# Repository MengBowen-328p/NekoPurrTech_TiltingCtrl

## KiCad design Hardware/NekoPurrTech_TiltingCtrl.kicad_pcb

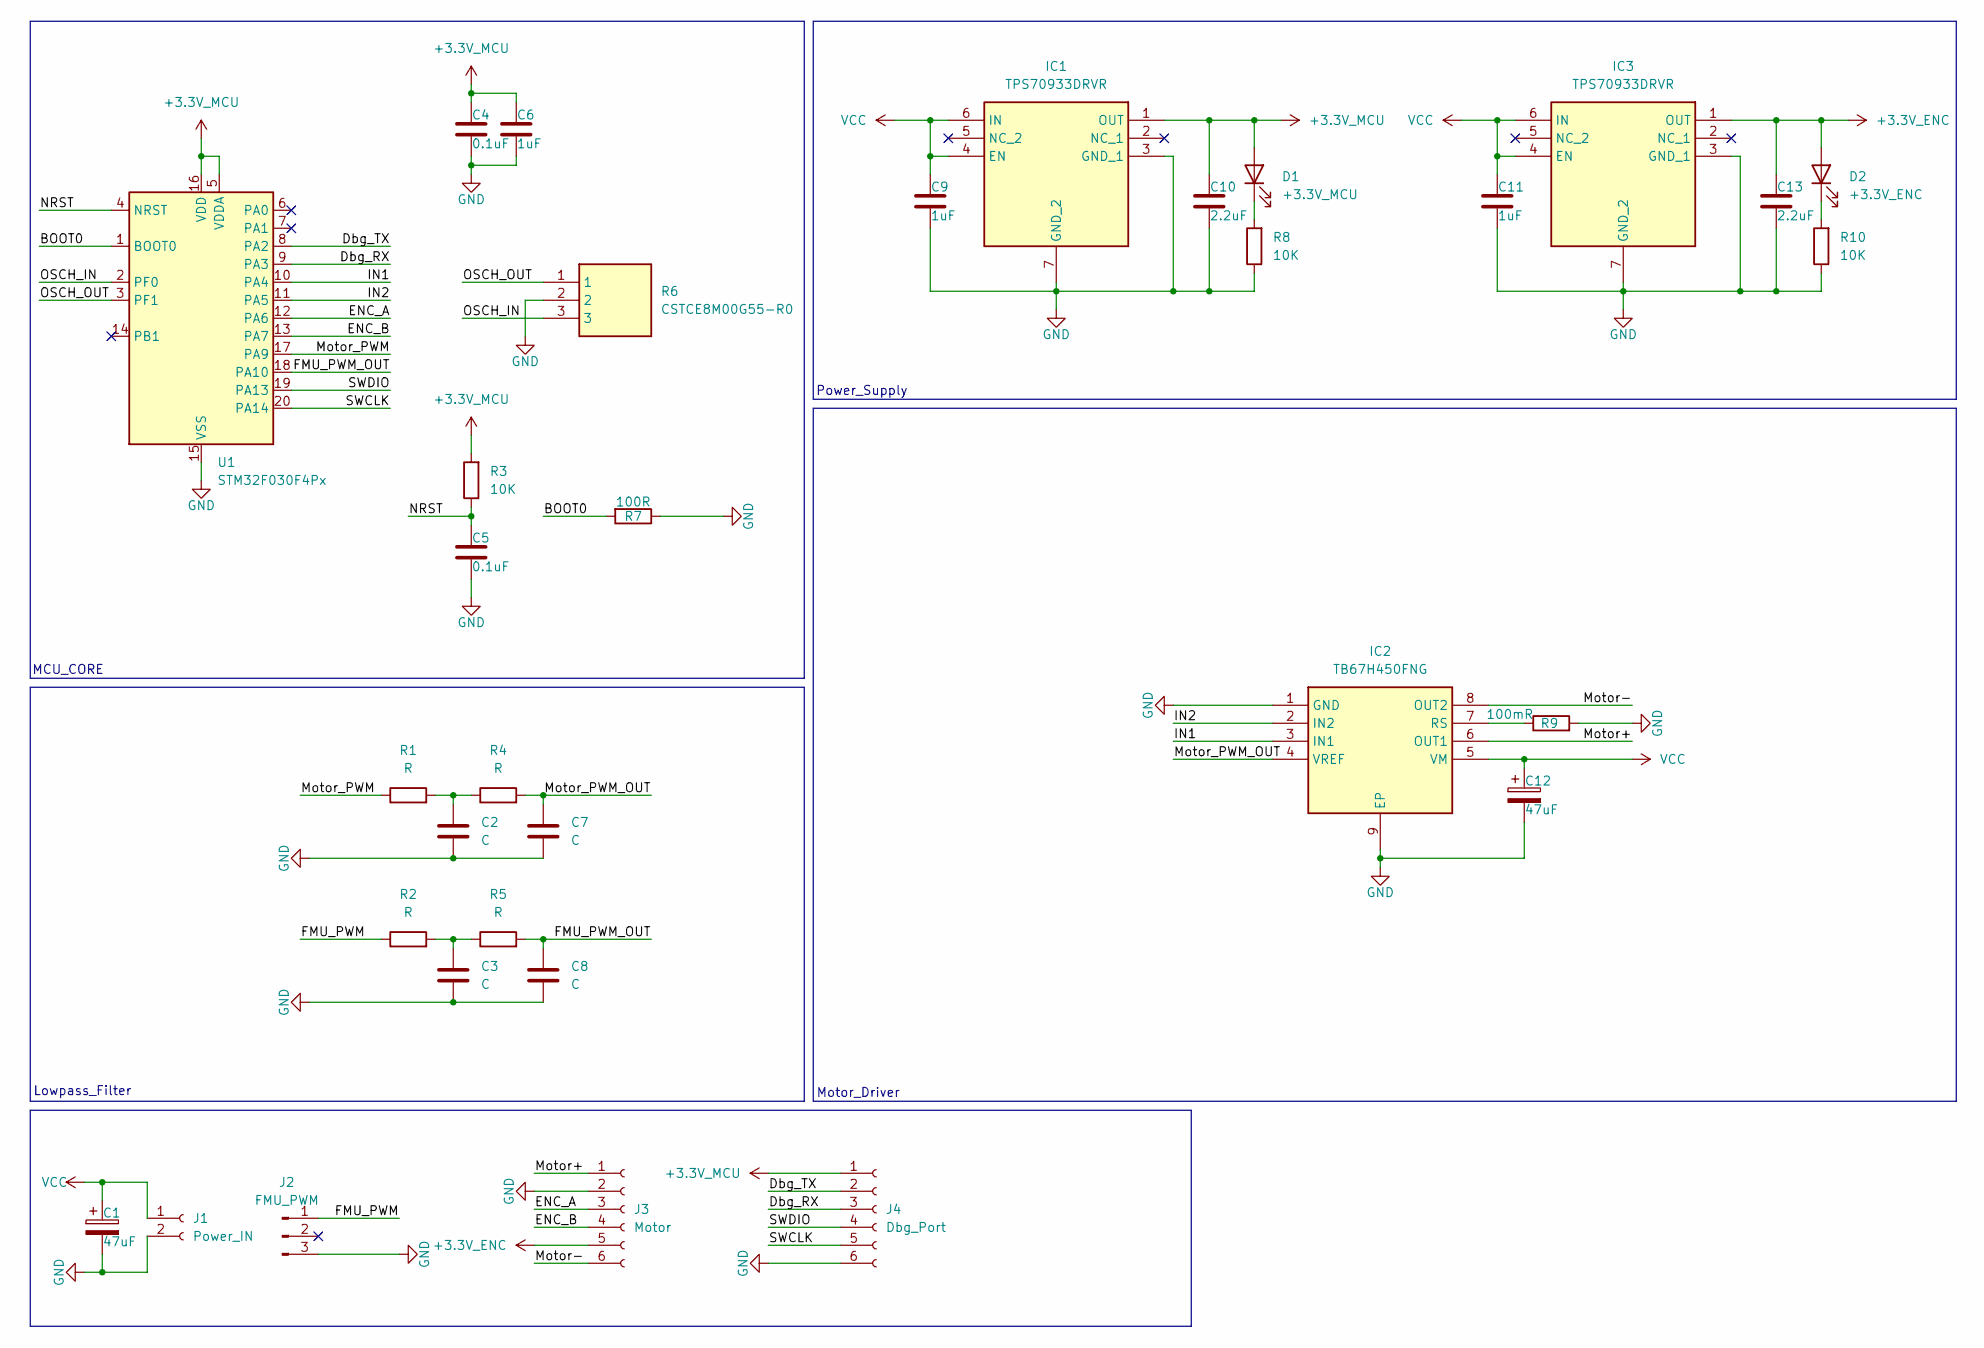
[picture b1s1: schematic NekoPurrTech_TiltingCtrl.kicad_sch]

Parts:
C1, C12: 47uF; CAPPM3528X210N
C2, C3, C7, C8: C; C_0603_1608Metric
C4, C5: 0.1uF; C_0603_1608Metric
C6, C9, C11: 1uF; C_0603_1608Metric
C10, C13: 2.2uF; C_0603_1608Metric
D1: +3.3V_MCU; LED_0603_1608Metric
D2: +3.3V_ENC; LED_0603_1608Metric
IC1, IC3: TPS70933DRVR; SON65P200X200X80-7N; Manufacturer_Part_Number TPS70933DRVR; Mouser Part Number 595-TPS70933DRVR
IC2: TB67H450FNG; SOIC127P600X175-9N; Manufacturer_Part_Number TB67H450FNG; Mouser Part Number N/A
J1: Power_IN; PinHeader_1x02_P2.54mm_Vertical
J2: FMU_PWM; PinHeader_1x03_P2.54mm_Vertical
J3: Motor; PinHeader_1x06_P2.54mm_Vertical
J4: Dbg_Port
R1, R2, R4, R5: R; R_0603_1608Metric
R3, R8, R10: 10K; R_0603_1608Metric
R6: CSTCE8M00G55-R0; CSTCE12M0G55-R0; Manufacturer_Part_Number CSTCE8M00G55-R0; Mouser Part Number 81-CSTCE8M00G55-R0
R7: 100R; R_0603_1608Metric
R9: 100mR; R_1206_3216Metric
U1: STM32F030F4Px; TSSOP-20_4.4x6.5mm_P0.65mm

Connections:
+3.3V_ENC: C13.1, D2.2 (A), IC3.1 (OUT), J3.5
+3.3V_MCU: C4.1, C6.1, C10.1, D1.2 (A), IC1.1 (OUT), J4.1, R3.2, U1.5 (VDDA), U1.16 (VDD)
/BOOT0: R7.2, U1.1 (BOOT0)
/Dbg_RX: J4.3, U1.9 (PA3)
/Dbg_TX: J4.2, U1.8 (PA2)
/ENC_A: J3.3, U1.12 (PA6)
/ENC_B: J3.4, U1.13 (PA7)
/FMU_PWM: J2.1, R2.1
/FMU_PWM_OUT: C8.1, R5.2, U1.18 (PA10)
/IN1: IC2.3 (IN1), U1.10 (PA4)
/IN2: IC2.2 (IN2), U1.11 (PA5)
/Motor+: IC2.6 (OUT1), J3.1
/Motor-: IC2.8 (OUT2), J3.6
/Motor_PWM: R1.1, U1.17 (PA9)
/Motor_PWM_OUT: C7.1, IC2.4 (VREF), R4.2
/NRST: C5.1, R3.1, U1.4 (NRST)
/OSCH_IN: R6.3, U1.2 (PF0)
/OSCH_OUT: R6.1, U1.3 (PF1)
/SWCLK: J4.5, U1.20 (PA14)
/SWDIO: J4.4, U1.19 (PA13)
GND: C1.2, C2.2, C3.2, C4.2, C5.2, C6.2, C7.2, C8.2, C9.2, C10.2, C11.2, C12.2, C13.2, IC1.3 (GND_1), IC1.7 (GND_2), IC2.1 (GND), IC2.9 (EP), IC3.3 (GND_1), IC3.7 (GND_2), J1.2, J2.3, J3.2, J4.6, R6.2, R7.1, R8.1, R9.2, R10.1, U1.15 (VSS)
unnamed: C2.1, R1.2, R4.1
unnamed: C3.1, R2.2, R5.1
unnamed: D1.1 (K), R8.2
unnamed: D2.1 (K), R10.2
unnamed: IC2.7 (RS), R9.1
VCC: C1.1, C9.1, C11.1, C12.1, IC1.4 (EN), IC1.6 (IN), IC2.5 (VM), IC3.4 (EN), IC3.6 (IN), J1.1

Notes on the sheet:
MCU_CORE
Lowpass_Filter
Motor_Driver
Power_Supply

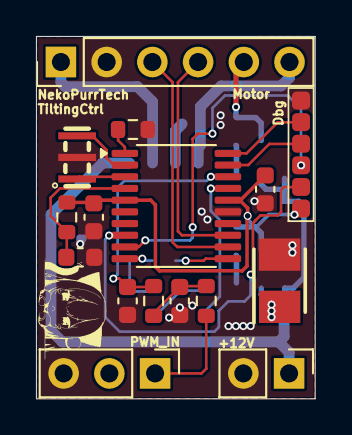
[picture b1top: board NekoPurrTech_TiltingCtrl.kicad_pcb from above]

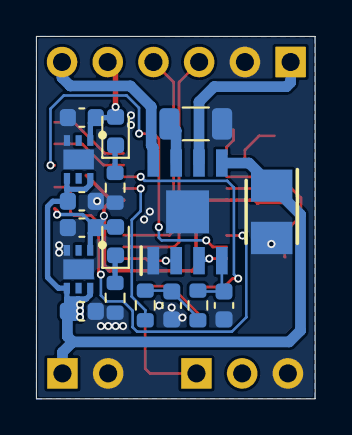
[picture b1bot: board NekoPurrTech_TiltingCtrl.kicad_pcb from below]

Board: 2 copper layers, 15.5 x 20.1 mm, 33 parts (17 on the bottom side), 27 nets.

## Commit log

2024-10-29 Finished Hardware
